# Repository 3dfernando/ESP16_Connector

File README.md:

# ESP16_Connector
Simple connector for the ESP-16 pressure transducer. The custom connector (12-pin) continually broke accidentally because its pins are exposed and very fragile. This is a fix for it. I'm assuming the Miniature DB-15 side of the cable is intact (usually true because that side is well-protected by a shell.)

BOM to fix this connector is very simple:
Just get 3x 4-pin header connectors with 0.018" (0.45mm) diameter pins. NORMAL HEADER CONNECTORS HAVE 0.75mm diameter pins. DON'T USE THOSE AS THEY DON'T FIT!!

Here's the connector I used:
https://www.digikey.com/en/products/detail/mill-max-manufacturing-corp/342-10-104-00-591000/4455942

Solder the headers according to the connection diagram inside the Pictures folder.

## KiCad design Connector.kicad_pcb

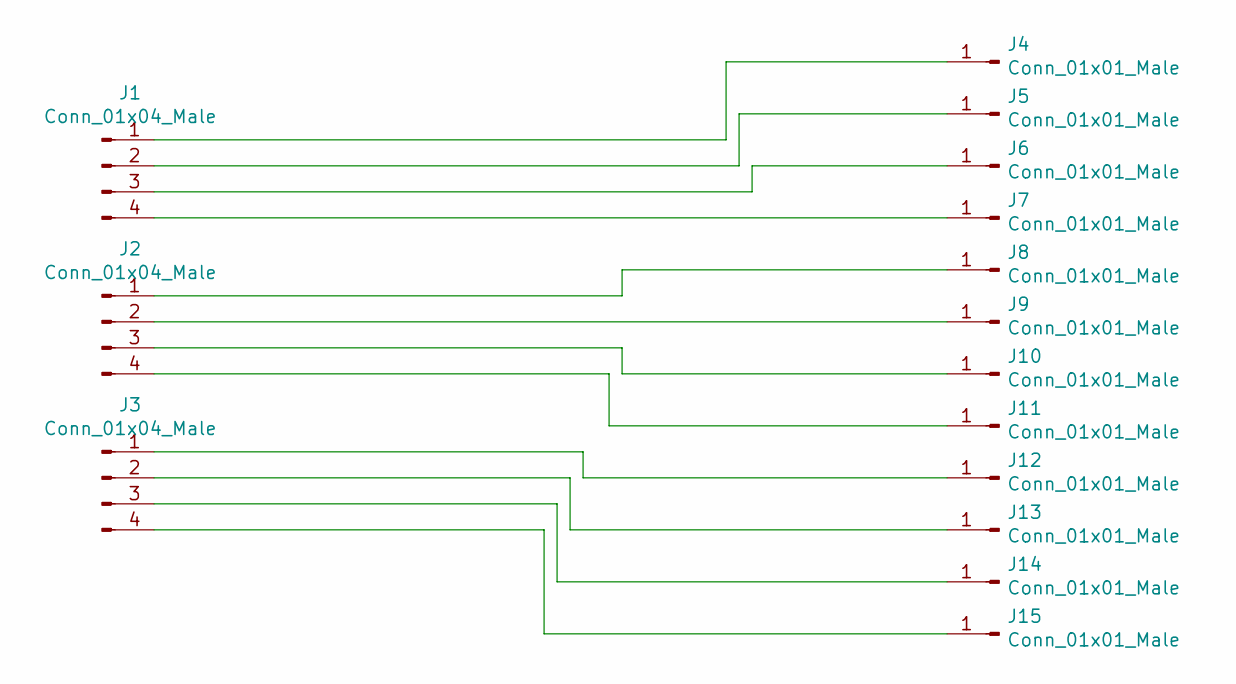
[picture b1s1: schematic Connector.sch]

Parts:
J1, J2, J3: Conn_01x04_Male; PinHeader_1x04_P2.54mm_Vertical
J4, J5, J6, J7, J8, J9, J10, J11, J12, J13, J14, J15: Conn_01x01_Male; PinHeader_1x01_P1.27mm_Vertical

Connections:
unnamed: J1.1, J4.1
unnamed: J1.2, J5.1
unnamed: J1.3, J6.1
unnamed: J1.4, J7.1
unnamed: J2.1, J8.1
unnamed: J2.2, J9.1
unnamed: J2.3, J10.1
unnamed: J2.4, J11.1
unnamed: J3.1, J12.1
unnamed: J3.2, J13.1
unnamed: J3.3, J14.1
unnamed: J3.4, J15.1

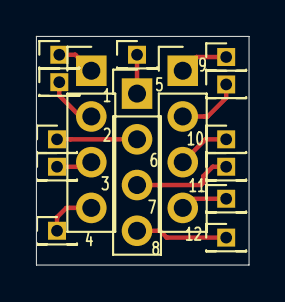
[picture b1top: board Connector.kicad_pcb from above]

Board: 2 copper layers, 11.8 x 12.7 mm, 15 parts (0 on the bottom side), 12 nets.

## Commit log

2021-09-29 Create A
